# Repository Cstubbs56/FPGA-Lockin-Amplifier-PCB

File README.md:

# FPGA-Lockin-Amplifier-PCB
## Purpose
This PCB acts as both DAQ and a lock in amplifier for the Waterloo Rocketry 2026 fiber optic gyroscope payload. To accomplish this, it 
- Biases the fibre optic loop by outputting a sinusoid to a piezoelectric crystal via a DAC with fibre optic wrapped around the PZT.
- Reads the output of the interferometer through a photodiode into a transimpedance amplifier and ADC.
- Calculates I and Q components then exports to an SD card going through the microcontroller.

## Power Electronics
The PCB needs 24V, 5V, 3.3V, 2.5V, and 1.2V. The 24V is used for biasing the piezoelectric crystal, and goes through a 0-20V output 16 bit DAC. 5V and 3.3V are used for the analog and digital circuitry, while the 2.5V and 1.2V are solely for powering the FPGA.

## Analog Electronics
As mentioned, there is an ADC reading a transimpedance amplifier. The transimpedance amplifier was sized based on an estimated maxium output power from the interferometer of 20mW into a photodiode with an approximate response of 0.55A/W. The other side is the aforementioned DAC, which is setup to output 0-20V with a sinusoid from the FPGA.

## Logging
The FPGA being used does nt have enough extra space in the fabric to interact with a filesystem and therefore the FPGA sends results to the microcontroller to be held in RAM before outputting to the SD card. There is a piece of flash memory connected to the FPGA, but this is used for configuration.

## FPGA
Since the FPGA's non-volatile configuration memory can only be written to once, the FPGA is used with volatile configuration. This means it must configure itself each time it powers on. It uses SPI for configuration, which is hooked up to both a flash ROM and a SPI header that can be used for programming the memory from a computer.  

## Laser
The laser on the PCB is a 200mW optical power infrared laser. It draws typically around 300mA in operation.

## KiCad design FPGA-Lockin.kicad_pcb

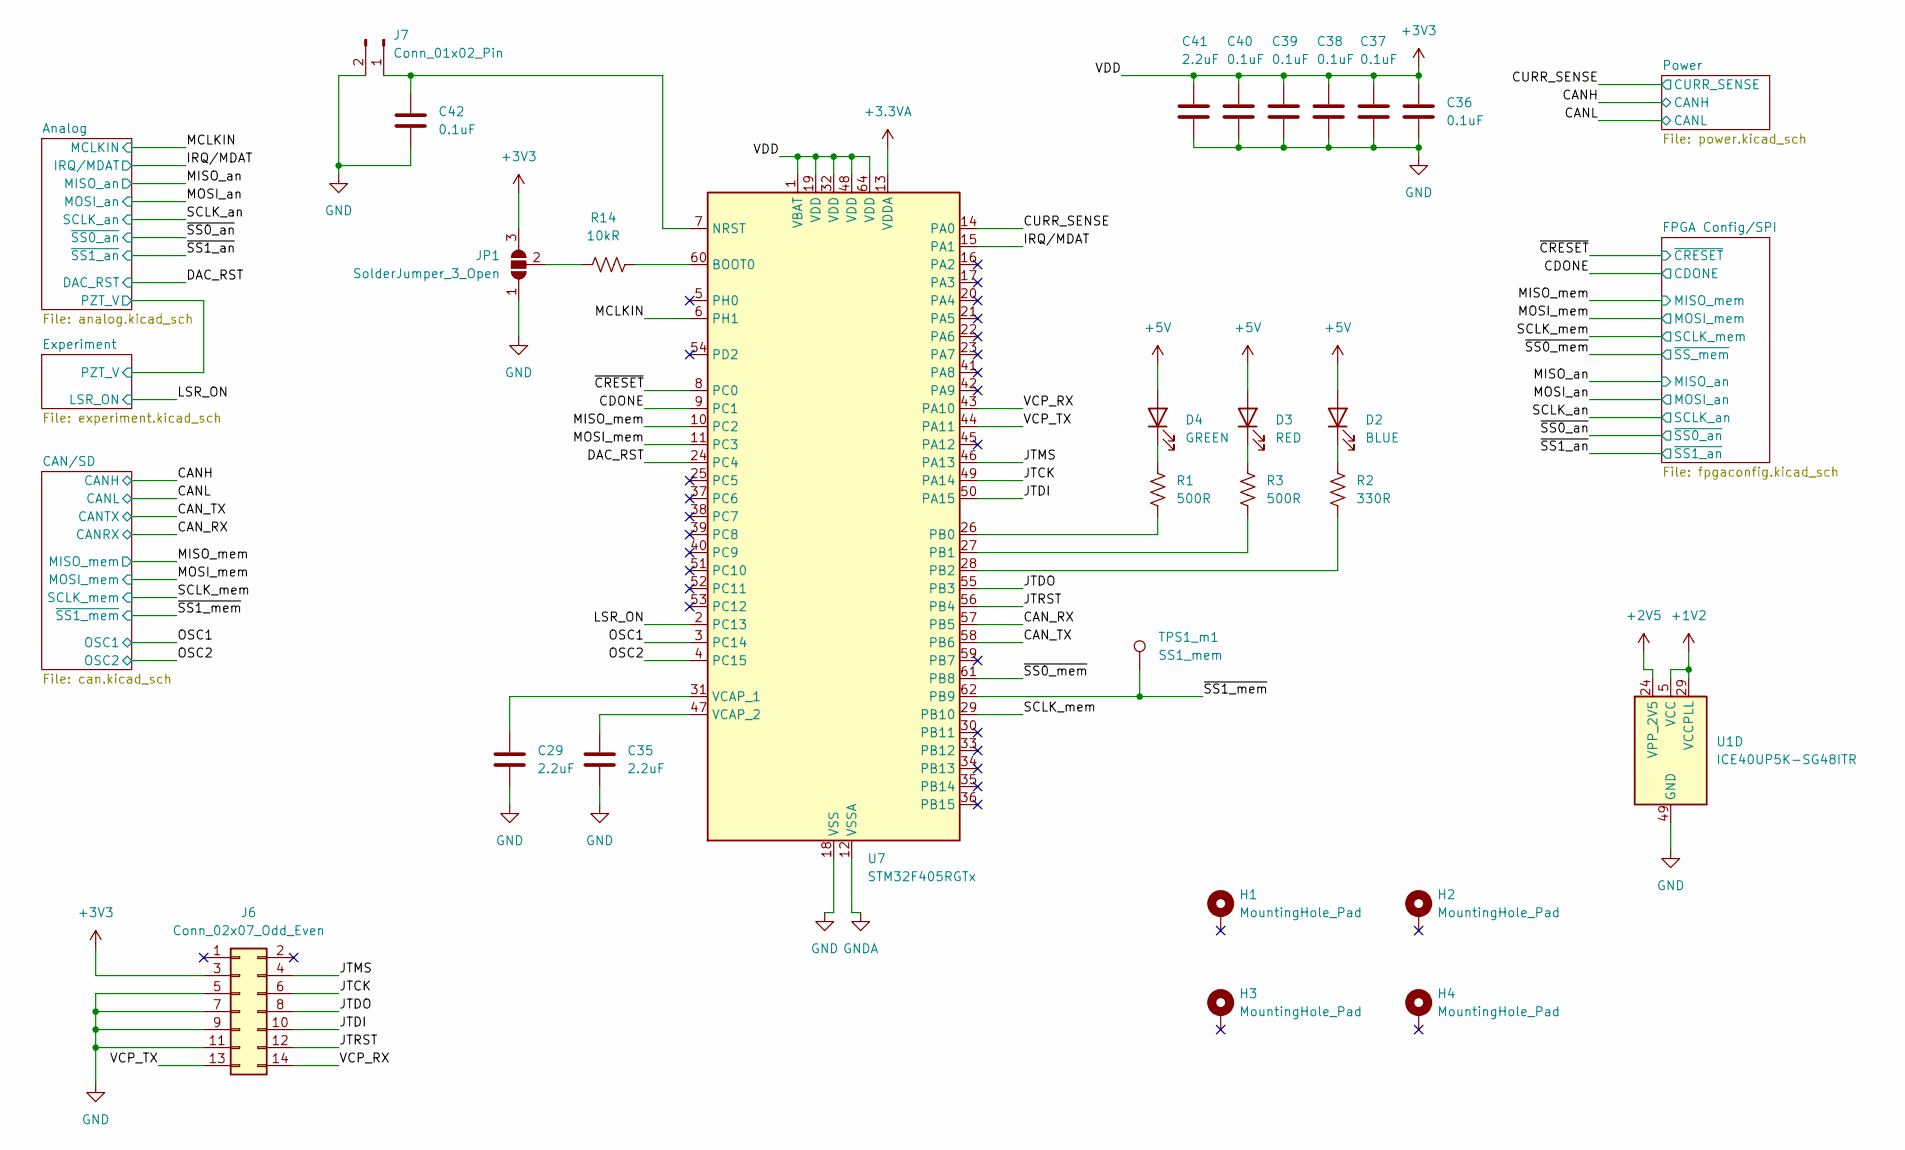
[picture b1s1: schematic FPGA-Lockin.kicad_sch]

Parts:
C29, C35, C41: 2.2uF; C_0805_2012Metric_Pad1.18x1.45mm_HandSolder
C36, C37, C38, C39, C40, C42: 0.1uF; C_0805_2012Metric_Pad1.18x1.45mm_HandSolder
D2: BLUE; LED_1206_3216Metric_Pad1.42x1.75mm_HandSolder
D3: RED; LED_1206_3216Metric_Pad1.42x1.75mm_HandSolder
D4: GREEN; LED_1206_3216Metric_Pad1.42x1.75mm_HandSolder
H1, H2, H3, H4: MountingHole_Pad; MountingHole_3.2mm_M3_Pad
J6: Conn_02x07_Odd_Even; PinSocket_2x07_P1.27mm_Vertical_SMD
J7: Conn_01x02_Pin; PinSocket_1x02_P2.54mm_Vertical
JP1: SolderJumper_3_Open; SolderJumper-3_P1.3mm_Open_RoundedPad1.0x1.5mm
R1, R3: 500R; R_0805_2012Metric_Pad1.20x1.40mm_HandSolder
R2: 330R; R_0805_2012Metric_Pad1.20x1.40mm_HandSolder
R14: 10kR; R_0805_2012Metric_Pad1.20x1.40mm_HandSolder
TPS1_m1: SS1_mem; TestPoint_Pad_D1.0mm
U1: ICE40UP5K-SG48ITR; QFN-48-1EP_7x7mm_P0.5mm_EP5.6x5.6mm
U7: STM32F405RGTx; LQFP-64_10x10mm_P0.5mm

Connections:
+1V2: U1.5 (VCC), U1.29 (VCCPLL), U1.30 (VCC); also elsewhere on the board
+2V5: U1.24 (VPP_2V5); also elsewhere on the board
+3.3VA: U7.13 (VDDA); also elsewhere on the board
+3V3: C36.1, C37.1, C38.1, C39.1, C40.1, C41.1, J6.3, JP1.3 (B), U7.1 (VBAT), U7.19 (VDD), U7.32 (VDD), U7.48 (VDD), U7.64 (VDD); also elsewhere on the board
+5V: D2.2 (A), D3.2 (A), D4.2 (A); also elsewhere on the board
/CAN_RX: U7.57 (PB5); also elsewhere on the board
/CAN_TX: U7.58 (PB6); also elsewhere on the board
/CDONE: U7.9 (PC1); also elsewhere on the board
/CURR_SENSE: U7.14 (PA0); also elsewhere on the board
/DAC_RST: U7.24 (PC4); also elsewhere on the board
/IRQ/MDAT: U7.15 (PA1); also elsewhere on the board
/JTCK: J6.6, U7.49 (PA14)
/JTDI: J6.10, U7.50 (PA15)
/JTDO: J6.8, U7.55 (PB3)
/JTMS: J6.4, U7.46 (PA13)
/JTRST: J6.12, U7.56 (PB4)
/LSR_ON: U7.2 (PC13); also elsewhere on the board
/MCLKIN: U7.6 (PH1); also elsewhere on the board
/MISO_mem: U7.10 (PC2); also elsewhere on the board
/MOSI_mem: U7.11 (PC3); also elsewhere on the board
/OSC1: U7.3 (PC14); also elsewhere on the board
/OSC2: U7.4 (PC15); also elsewhere on the board
/SCLK_mem: U7.29 (PB10); also elsewhere on the board
/VCP_RX: J6.14, U7.43 (PA10)
/VCP_TX: J6.13, U7.44 (PA11)
/~CRESET: U7.8 (PC0); also elsewhere on the board
/~SS0_mem: U7.61 (PB8); also elsewhere on the board
/~SS1_mem: TPS1_m1.1, U7.62 (PB9); also elsewhere on the board
GND: C29.2, C35.2, C36.2, C37.2, C38.2, C39.2, C40.2, C41.2, C42.2, J6.5, J6.7, J6.9, J6.11, J7.2, JP1.1 (A), U1.49 (GND), U7.18 (VSS), U7.63 (VSS); also elsewhere on the board
GNDA: U7.12 (VSSA); also elsewhere on the board
unnamed: D2.1 (K), R2.1
unnamed: D3.1 (K), R3.1
unnamed: D4.1 (K), R1.1
unnamed: C42.1, J7.1, U7.7 (NRST)
unnamed: JP1.2 (C), R14.2
unnamed: R14.1, U7.60 (BOOT0)
unnamed: R1.2, U7.26 (PB0)
unnamed: R3.2, U7.27 (PB1)
unnamed: R2.2, U7.28 (PB2)
unnamed: C29.1, U7.31 (VCAP_1)
unnamed: C35.1, U7.47 (VCAP_2)

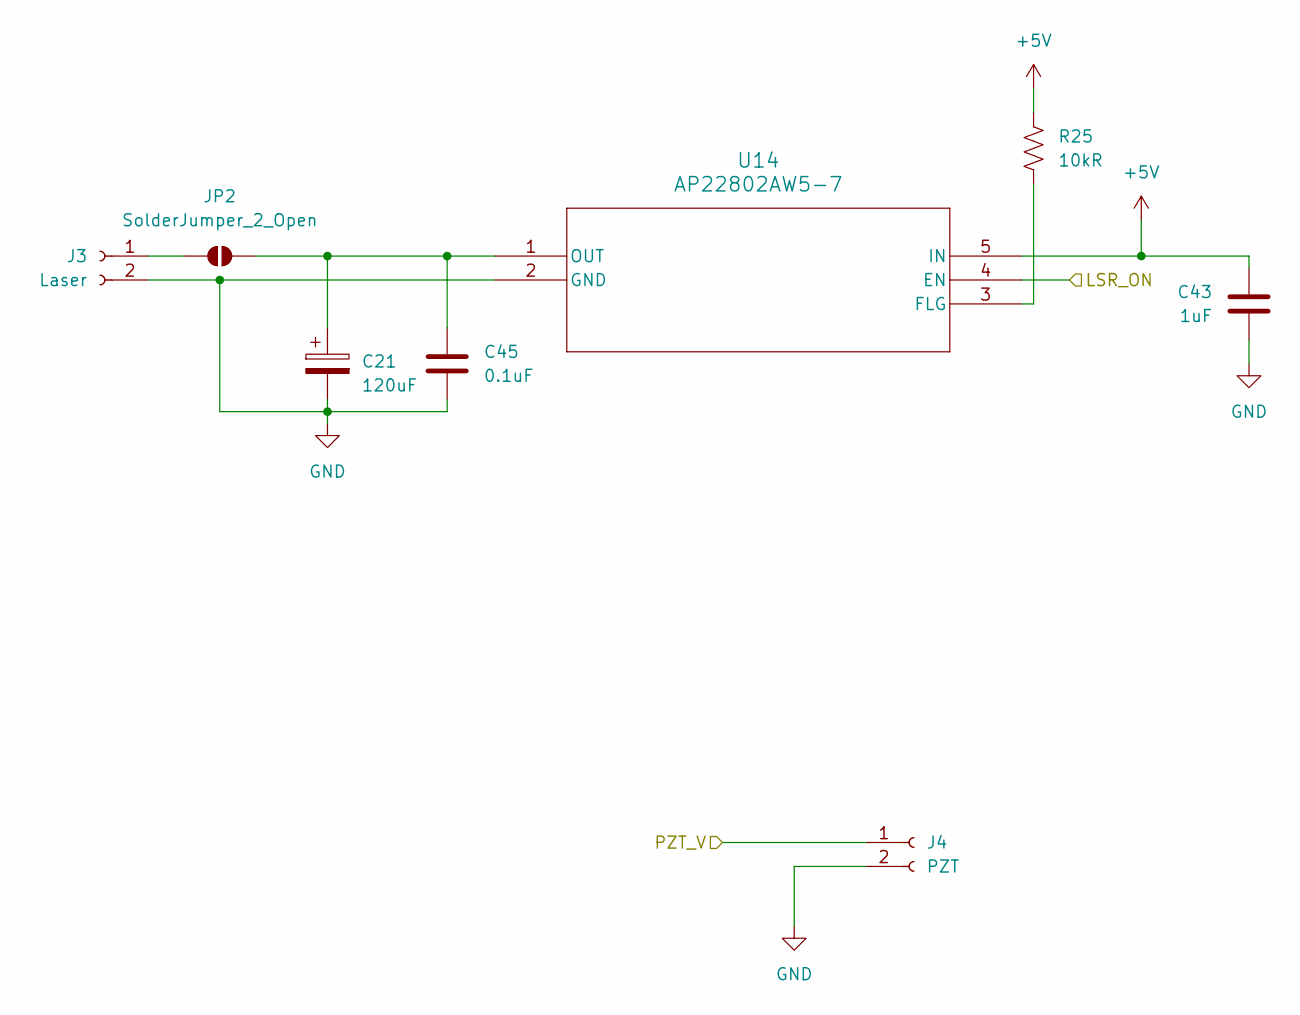
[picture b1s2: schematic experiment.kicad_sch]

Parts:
C21: 120uF; CP_EIA-7132-20_AVX-U_HandSolder
C43: 1uF; C_0805_2012Metric_Pad1.18x1.45mm_HandSolder
C45: 0.1uF; C_0805_2012Metric_Pad1.18x1.45mm_HandSolder
J3: Laser; 691137710002
J4: PZT; 691137710002
JP2: SolderJumper_2_Open; SolderJumper-2_P1.3mm_Open_RoundedPad1.0x1.5mm
R25: 10kR; R_0805_2012Metric_Pad1.20x1.40mm_HandSolder
U14: AP22802AW5-7; SOT25_DIO

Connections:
+5V: C43.2, R25.1, U14.5 (IN); also elsewhere on the board
/Analog/PZT_V: J4.1; also elsewhere on the board
/LSR_ON: U14.4 (EN); also elsewhere on the board
GND: C21.2, C43.1, C45.2, J3.2, J4.2, U14.2 (GND); also elsewhere on the board
unnamed: J3.1, JP2.2 (B)
unnamed: C21.1, C45.1, JP2.1 (A), U14.1 (OUT)
unnamed: R25.2, U14.3 (FLG)

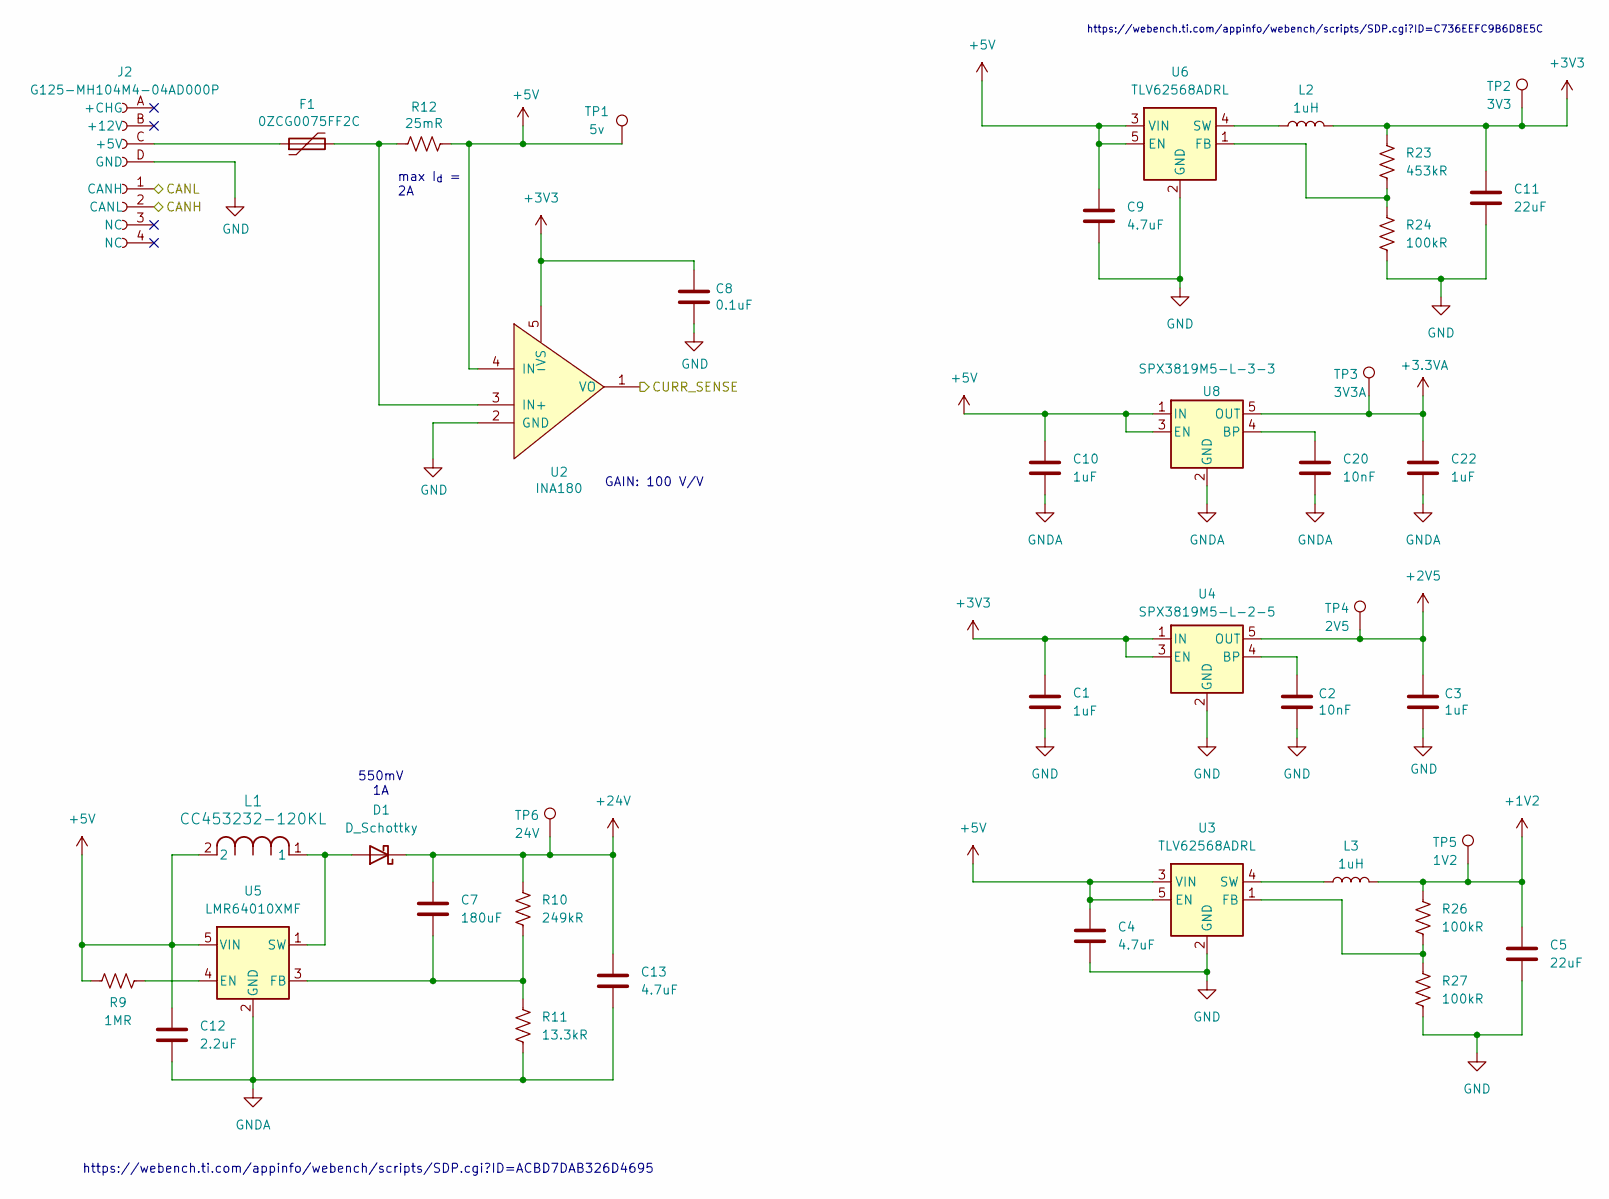
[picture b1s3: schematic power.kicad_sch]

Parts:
C1, C10, C22: 1uF; C_0805_2012Metric_Pad1.18x1.45mm_HandSolder
C2: 10nF; C_0805_2012Metric_Pad1.18x1.45mm_HandSolder; DigiKey 732-12169-1-ND
C3: 1uF; C_0805_2012Metric_Pad1.18x1.45mm_HandSolder; DigiKey 1276-6470-1-ND
C4, C9: 4.7uF; C_0805_2012Metric_Pad1.18x1.45mm_HandSolder
C5, C11: 22uF; C_0805_2012Metric_Pad1.18x1.45mm_HandSolder
C7: 180uF; C_1210_3225Metric_Pad1.33x2.70mm_HandSolder
C8: 0.1uF; C_0805_2012Metric_Pad1.18x1.45mm_HandSolder; DigiKey 311-1858-1-ND
C12: 2.2uF; C_0805_2012Metric_Pad1.18x1.45mm_HandSolder
C13: 4.7uF; C_1210_3225Metric_Pad1.33x2.70mm_HandSolder
C20: 10nF; C_0805_2012Metric_Pad1.18x1.45mm_HandSolder
D1: D_Schottky; DIO_RB051MM_ROM
F1: 0ZCG0075FF2C; Fuse_1812_4532Metric_Pad1.30x3.40mm_HandSolder; DigiKey F3732CT-ND
J2: G125-MH104M4-04AD000P; connector_Harwin_G125-MH104M4-04AD000P
L1: CC453232-120KL; IND_BOURNS_CC453232
L2, L3: 1uH; L_1206_3216Metric_Pad1.22x1.90mm_HandSolder
R9: 1MR; R_0805_2012Metric_Pad1.20x1.40mm_HandSolder
R10: 249kR; R_0805_2012Metric_Pad1.20x1.40mm_HandSolder
R11: 13.3kR; R_0805_2012Metric_Pad1.20x1.40mm_HandSolder
R12: 25mR; R_0805_2012Metric_Pad1.20x1.40mm_HandSolder; DigiKey WSLB-.20CT-ND
R23: 453kR; R_0805_2012Metric_Pad1.20x1.40mm_HandSolder
R24, R26, R27: 100kR; R_0805_2012Metric_Pad1.20x1.40mm_HandSolder
TP1: 5v; TestPoint_Pad_1.5x1.5mm
TP2: 3V3; TestPoint_Pad_1.5x1.5mm
TP3: 3V3A; TestPoint_Pad_1.5x1.5mm
TP4: 2V5; TestPoint_Pad_1.5x1.5mm
TP5: 1V2; TestPoint_Pad_1.5x1.5mm
TP6: 24V; TestPoint_Pad_1.5x1.5mm
U2: INA180; SOT-23-5_HandSoldering; DigiKey 296-INA180A3QDBVRQ1CT-ND
U3, U6: TLV62568ADRL; SOT-563
U4: SPX3819M5-L-2-5; SOT-23-5
U5: LMR64010XMF; SOT-23-5
U8: SPX3819M5-L-3-3; SOT-23-5_HandSoldering; DigiKey 1016-1873-1-ND

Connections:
+1V2: C5.1, L3.2, R26.1, TP5.1; also elsewhere on the board
+2V5: C3.1, TP4.1, U4.5 (OUT); also elsewhere on the board
+3.3VA: C22.1, TP3.1, U8.5 (OUT); also elsewhere on the board
+3V3: C1.1, C8.1, C11.1, L2.2, R23.1, TP2.1, U2.5 (VS), U4.1 (IN), U4.3 (EN); also elsewhere on the board
+5V: C4.1, C9.1, C10.1, C12.1, L1.2, R9.2, R12.1, TP1.1, U2.4 (IN-), U3.3 (VIN), U3.5 (EN), U5.5 (VIN), U6.3 (VIN), U6.5 (EN), U8.1 (IN), U8.3 (EN); also elsewhere on the board
+24V: C7.1, C13.1, D1.1 (K), R10.1, TP6.1; also elsewhere on the board
/CANH: J2.2 (CANL); also elsewhere on the board
/CANL: J2.1 (CANH); also elsewhere on the board
/CURR_SENSE: U2.1 (VO); also elsewhere on the board
GND: C1.2, C2.2, C3.2, C4.2, C5.2, C8.2, C9.2, C11.2, J2.D (GND), R24.2, R27.2, U2.2 (GND), U3.2 (GND), U4.2 (GND), U6.2 (GND); also elsewhere on the board
GNDA: C10.2, C12.2, C13.2, C20.2, C22.2, R11.2, U5.2 (GND), U8.2 (GND); also elsewhere on the board
unnamed: D1.2 (A), L1.1, U5.1 (SW)
unnamed: F1.1, J2.C (+5V)
unnamed: F1.2, R12.2, U2.3 (IN+)
unnamed: R26.2, R27.1, U3.1 (FB)
unnamed: L3.1, U3.4 (SW)
unnamed: C2.1, U4.4 (BP)
unnamed: R9.1, U5.4 (EN)
unnamed: C7.2, R10.2, R11.1, U5.3 (FB)
unnamed: R23.2, R24.1, U6.1 (FB)
unnamed: L2.1, U6.4 (SW)
unnamed: C20.1, U8.4 (BP)

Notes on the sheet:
GAIN: 100 V/V
https://webench.ti.com/appinfo/webench/scripts/SDP.cgi?ID=C736EEFC9B6D8E5C
max I_{d} = 2A
550mV 1A
https://webench.ti.com/appinfo/webench/scripts/SDP.cgi?ID=ACBD7DAB326D4695

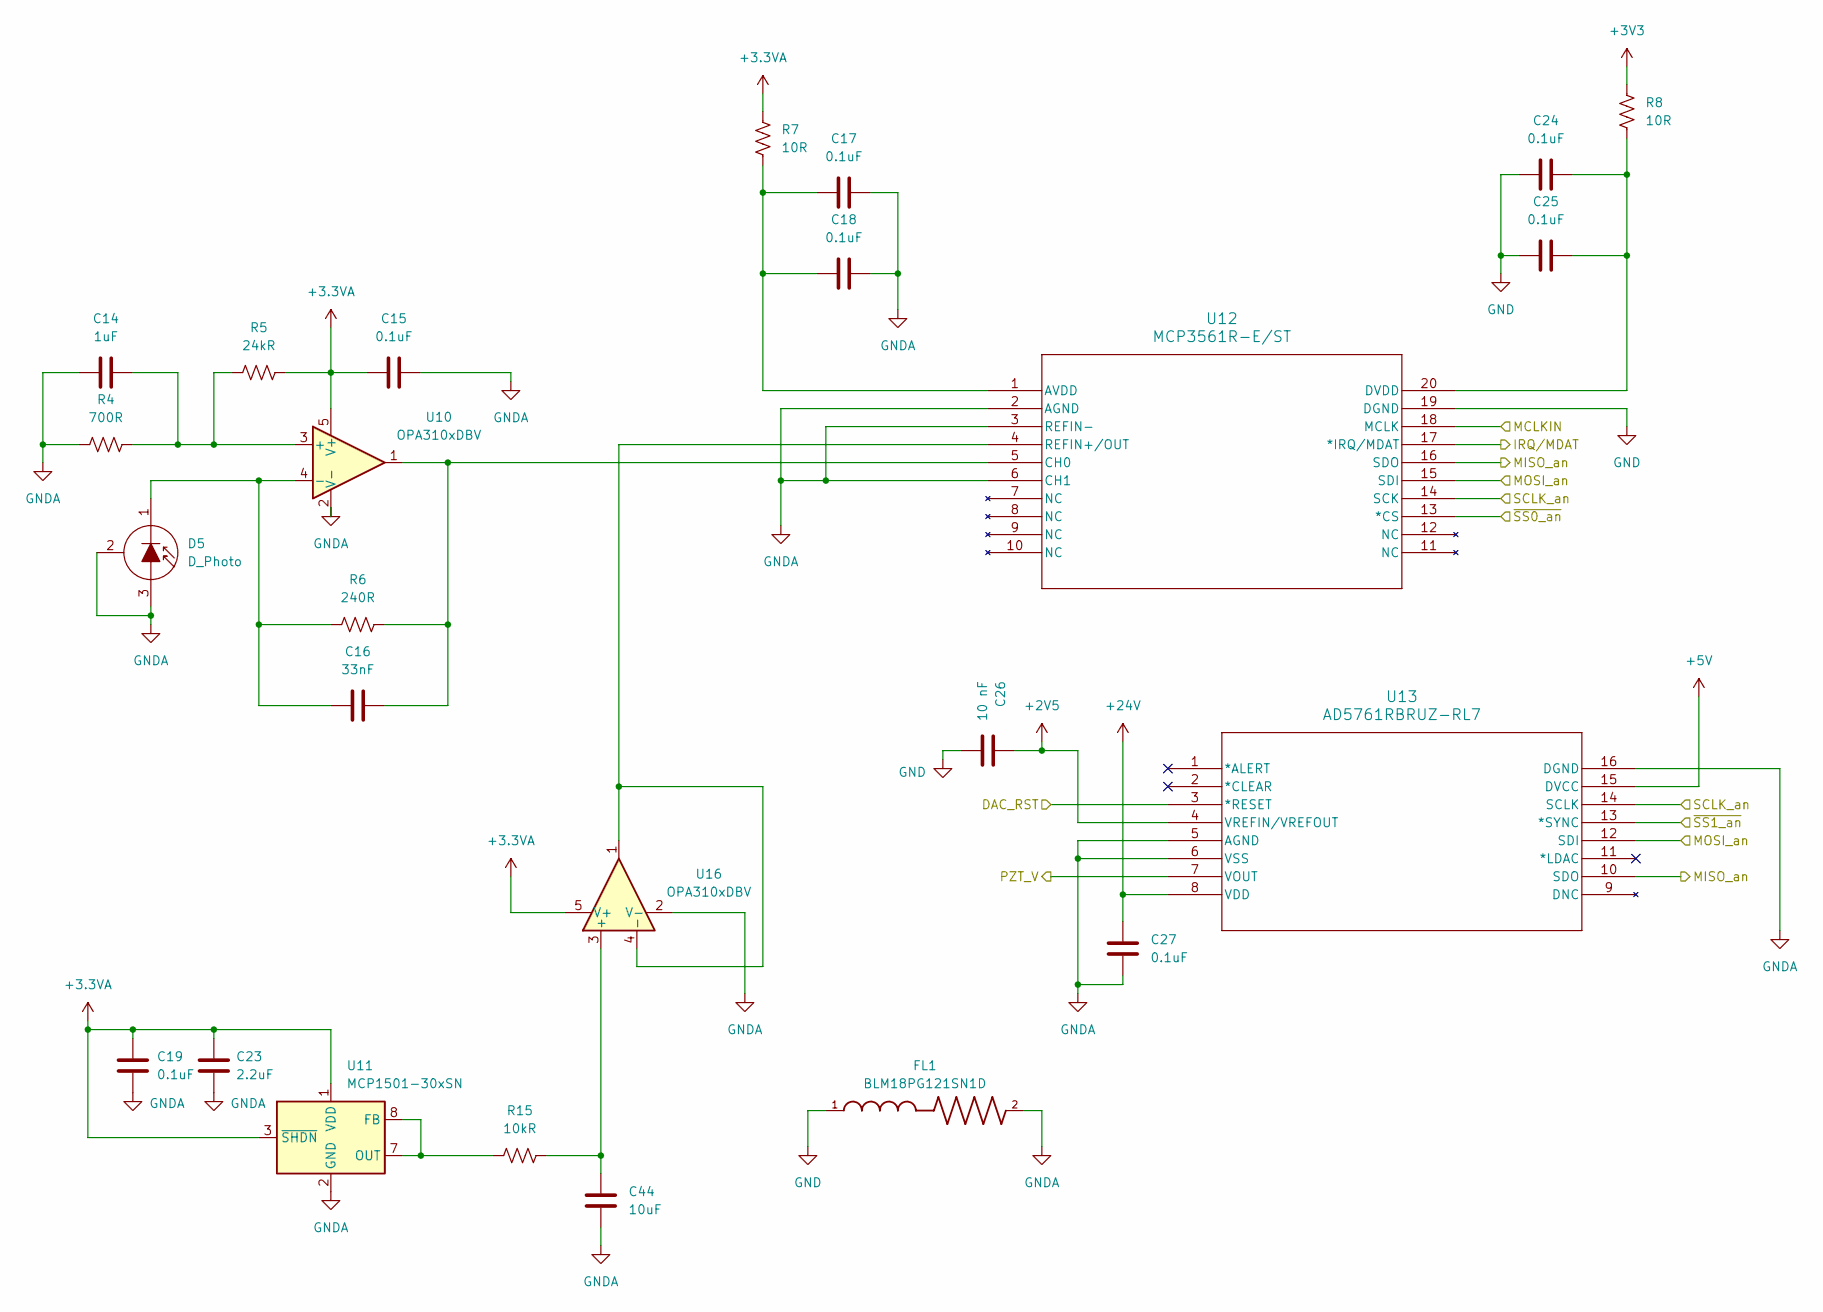
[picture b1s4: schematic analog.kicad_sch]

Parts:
C14: 1uF; C_0805_2012Metric_Pad1.18x1.45mm_HandSolder
C15, C17, C18, C19, C24, C25: 0.1uF; C_0805_2012Metric_Pad1.18x1.45mm_HandSolder
C16: 33nF; C_0805_2012Metric_Pad1.18x1.45mm_HandSolder
C23: 2.2uF; C_0805_2012Metric_Pad1.18x1.45mm_HandSolder
C26: 10 nF; C_0805_2012Metric_Pad1.18x1.45mm_HandSolder
C27: 0.1uF; C_1210_3225Metric_Pad1.33x2.70mm_HandSolder
C44: 10uF; C_0805_2012Metric_Pad1.18x1.45mm_HandSolder
D5: D_Photo; TO-5-3
FL1: BLM18PG121SN1D; BEADC1608X95N
R4: 700R; R_0805_2012Metric_Pad1.20x1.40mm_HandSolder
R5: 24kR; R_0805_2012Metric_Pad1.20x1.40mm_HandSolder
R6: 240R; R_0805_2012Metric_Pad1.20x1.40mm_HandSolder
R7, R8: 10R; R_0805_2012Metric_Pad1.20x1.40mm_HandSolder
R15: 10kR; R_0805_2012Metric_Pad1.20x1.40mm_HandSolder
U10, U16: OPA310xDBV; SOT-23-5
U11: MCP1501-30xSN; SOIC-8_3.9x4.9mm_P1.27mm
U12: MCP3561R-E/ST; TSSOP20_ST_MCH
U13: AD5761RBRUZ-RL7; RU-16_ADI

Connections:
+2V5: C26.1, U13.4 (VREFIN/VREFOUT); also elsewhere on the board
+3.3VA: C15.2, C19.1, C23.1, R5.2, R7.1, U10.5 (V+), U11.1 (VDD), U11.3 (~SHDN), U16.5 (V+); also elsewhere on the board
+3V3: R8.1; also elsewhere on the board
+5V: U13.15 (DVCC); also elsewhere on the board
+24V: C27.1, U13.8 (VDD); also elsewhere on the board
/Analog/PZT_V: U13.7 (VOUT); also elsewhere on the board
/DAC_RST: U13.3 (*RESET); also elsewhere on the board
/IRQ/MDAT: U12.17 (*IRQ/MDAT); also elsewhere on the board
/MCLKIN: U12.18 (MCLK); also elsewhere on the board
/MISO_an: U12.16 (SDO), U13.10 (SDO); also elsewhere on the board
/MOSI_an: U12.15 (SDI), U13.12 (SDI); also elsewhere on the board
/SCLK_an: U12.14 (SCK), U13.14 (SCLK); also elsewhere on the board
/~SS0_an: U12.13 (*CS); also elsewhere on the board
/~SS1_an: U13.13 (*SYNC); also elsewhere on the board
GND: C24.1, C25.1, C26.2, FL1.1, U12.19 (DGND); also elsewhere on the board
GNDA: C14.2, C15.1, C17.2, C18.2, C19.2, C23.2, C27.2, C44.2, D5.2 (C), D5.3 (A), FL1.2, R4.1, U10.2 (V-), U11.2 (GND), U11.4 (GND), U11.5 (GND), U11.6 (GND), U12.2 (AGND), U12.3 (REFIN-), U12.6 (CH1), U13.5 (AGND), U13.6 (VSS), U13.16 (DGND), U16.2 (V-); also elsewhere on the board
unnamed: C16.2, D5.1 (K), R6.1, U10.4 (-)
unnamed: C14.1, R4.2, R5.1, U10.3 (+)
unnamed: R15.1, U11.7 (OUT), U11.8 (FB)
unnamed: C17.1, C18.1, R7.2, U12.1 (AVDD)
unnamed: C16.1, R6.2, U10.1, U12.5 (CH0)
unnamed: C24.2, C25.2, R8.2, U12.20 (DVDD)
unnamed: U12.4 (REFIN+/OUT), U16.1, U16.4 (-)
unnamed: C44.1, R15.2, U16.3 (+)

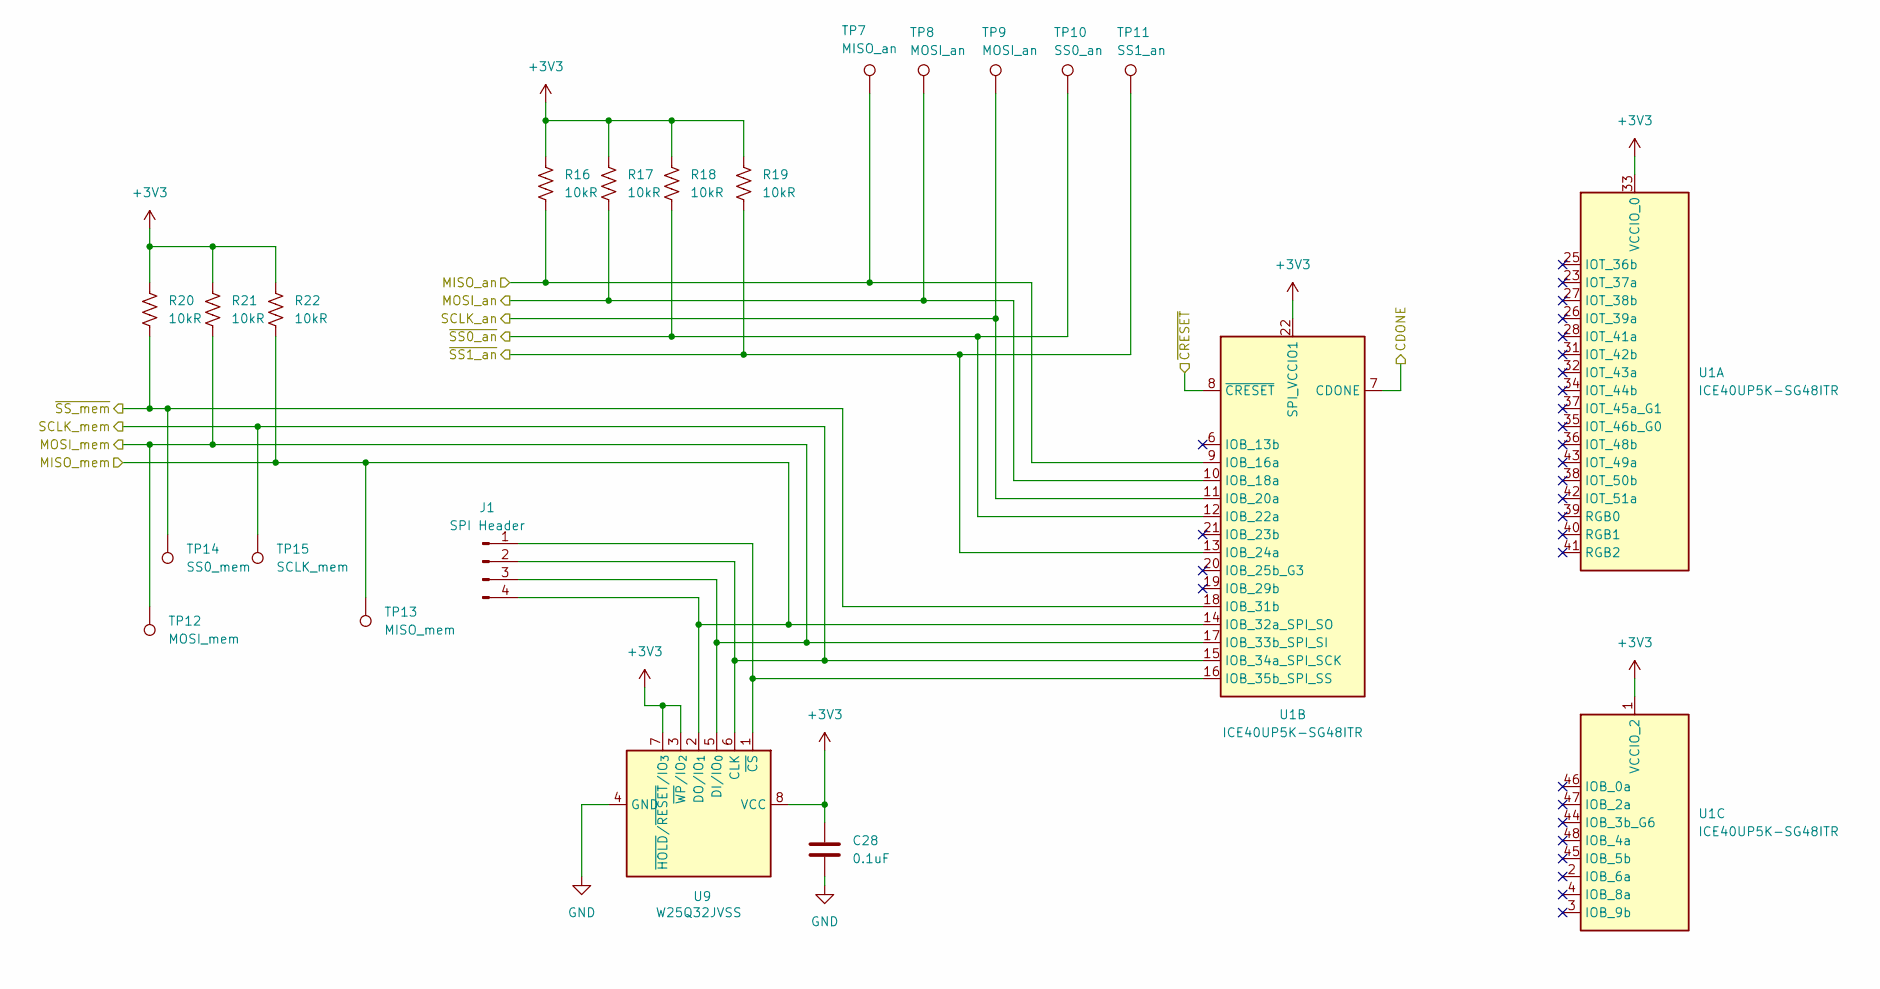
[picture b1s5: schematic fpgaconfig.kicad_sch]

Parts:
C28: 0.1uF; C_0805_2012Metric_Pad1.18x1.45mm_HandSolder
J1: SPI Header; PinHeader_1x04_P2.54mm_Vertical
R16, R17, R18, R19, R20, R21, R22: 10kR; R_0805_2012Metric_Pad1.20x1.40mm_HandSolder
TP7: MISO_an; TestPoint_Pad_D1.0mm
TP8, TP9: MOSI_an; TestPoint_Pad_D1.0mm
TP10: SS0_an; TestPoint_Pad_D1.0mm
TP11: SS1_an; TestPoint_Pad_D1.0mm
TP12: MOSI_mem; TestPoint_Pad_D1.0mm
TP13: MISO_mem; TestPoint_Pad_D1.0mm
TP14: SS0_mem; TestPoint_Pad_D1.0mm
TP15: SCLK_mem; TestPoint_Pad_D1.0mm
U1: ICE40UP5K-SG48ITR; QFN-48-1EP_7x7mm_P0.5mm_EP5.6x5.6mm
U9: W25Q32JVSS; SOIC-8_5.3x5.3mm_P1.27mm

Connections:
+3V3: C28.1, R16.1, R17.1, R18.1, R19.1, R20.1, R21.1, R22.1, U1.1 (VCCIO_2), U1.22 (SPI_VCCIO1), U1.33 (VCCIO_0), U9.3 (~WP/IO_{2}), U9.7 (~HOLD/~RESET/IO_{3}), U9.8 (VCC); also elsewhere on the board
/CDONE: U1.7 (CDONE); also elsewhere on the board
/MISO_an: R16.2, TP7.1, U1.9 (IOB_16a); also elsewhere on the board
/MISO_mem: J1.4, R22.2, TP13.1, U1.14 (IOB_32a_SPI_SO), U9.2 (DO/IO_{1}); also elsewhere on the board
/MOSI_an: R17.2, TP8.1, U1.10 (IOB_18a); also elsewhere on the board
/MOSI_mem: J1.3, R21.2, TP12.1, U1.17 (IOB_33b_SPI_SI), U9.5 (DI/IO_{0}); also elsewhere on the board
/SCLK_an: TP9.1, U1.11 (IOB_20a); also elsewhere on the board
/SCLK_mem: J1.2, TP15.1, U1.15 (IOB_34a_SPI_SCK), U9.6 (CLK); also elsewhere on the board
/~CRESET: U1.8 (~CRESET); also elsewhere on the board
/~SS0_an: R18.2, TP10.1, U1.12 (IOB_22a); also elsewhere on the board
/~SS0_mem: R20.2, TP14.1, U1.18 (IOB_31b); also elsewhere on the board
/~SS1_an: R19.2, TP11.1, U1.13 (IOB_24a); also elsewhere on the board
GND: C28.2, U9.4 (GND); also elsewhere on the board
unnamed: J1.1, U1.16 (IOB_35b_SPI_SS), U9.1 (~CS)

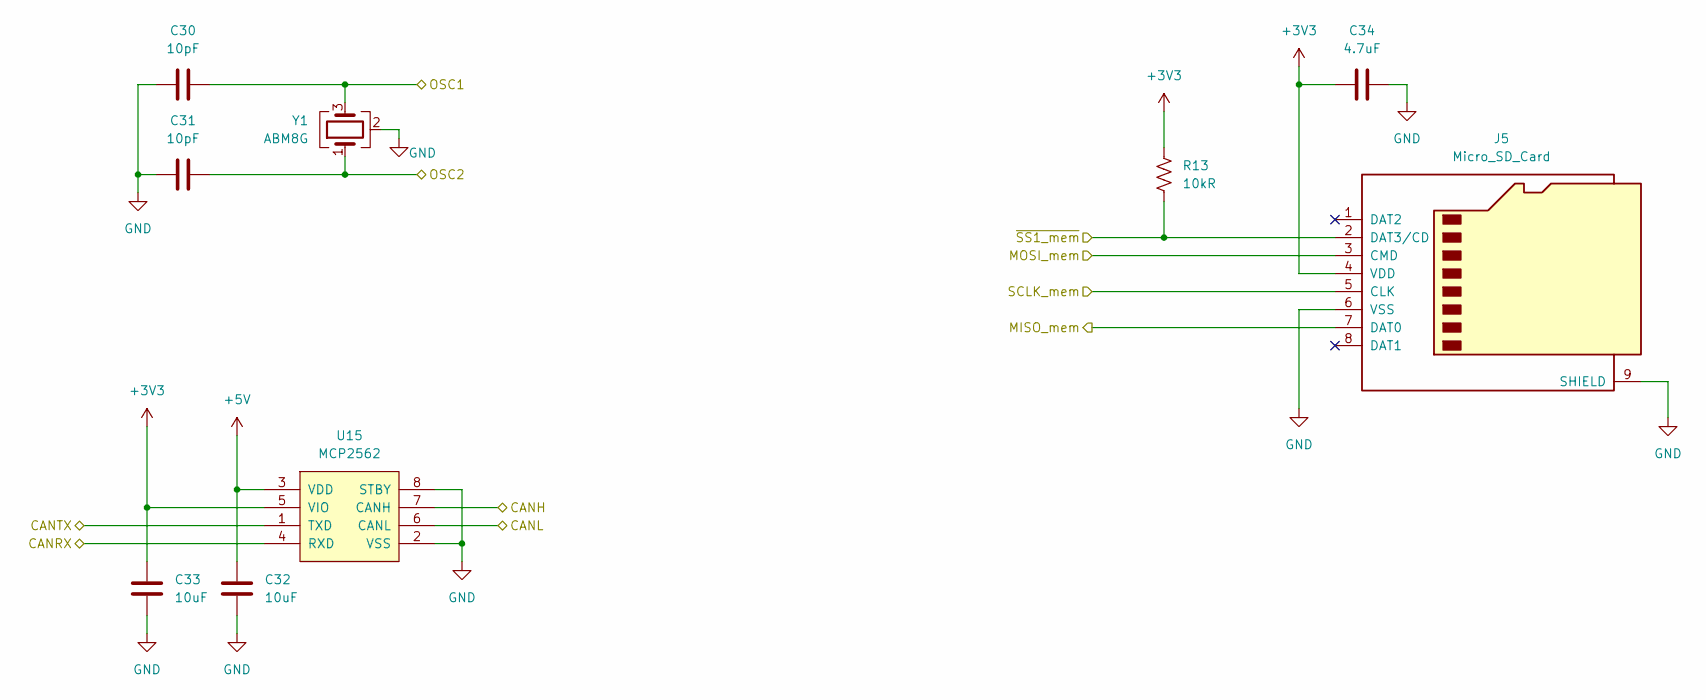
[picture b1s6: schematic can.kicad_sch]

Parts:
C30, C31: 10pF; C_0805_2012Metric_Pad1.18x1.45mm_HandSolder
C32, C33: 10uF; C_0805_2012Metric_Pad1.18x1.45mm_HandSolder
C34: 4.7uF; C_0805_2012Metric_Pad1.18x1.45mm_HandSolder
J5: Micro_SD_Card; microSD_Molex_WM6698CT-ND
R13: 10kR; R_0805_2012Metric_Pad1.20x1.40mm_HandSolder
U15: MCP2562; SOIC-8_3.9x4.9mm_P1.27mm
Y1: ABM8G; Crystal_SMD_Abracon_ABM8G-4Pin_3.2x2.5mm

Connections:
+3V3: C33.1, C34.2, J5.4 (VDD), R13.1, U15.5 (VIO); also elsewhere on the board
+5V: C32.1, U15.3 (VDD); also elsewhere on the board
/CANH: U15.7 (CANH); also elsewhere on the board
/CANL: U15.6 (CANL); also elsewhere on the board
/CAN_RX: U15.4 (RXD); also elsewhere on the board
/CAN_TX: U15.1 (TXD); also elsewhere on the board
/MISO_mem: J5.7 (DAT0); also elsewhere on the board
/MOSI_mem: J5.3 (CMD); also elsewhere on the board
/OSC1: C30.2, Y1.3; also elsewhere on the board
/OSC2: C31.2, Y1.1; also elsewhere on the board
/SCLK_mem: J5.5 (CLK); also elsewhere on the board
/~SS1_mem: J5.2 (DAT3/CD), R13.2; also elsewhere on the board
GND: C30.1, C31.1, C32.2, C33.2, C34.1, J5.6 (VSS), J5.9 (SHIELD), U15.2 (VSS), U15.8 (STBY), Y1.2 (G), Y1.4 (G); also elsewhere on the board

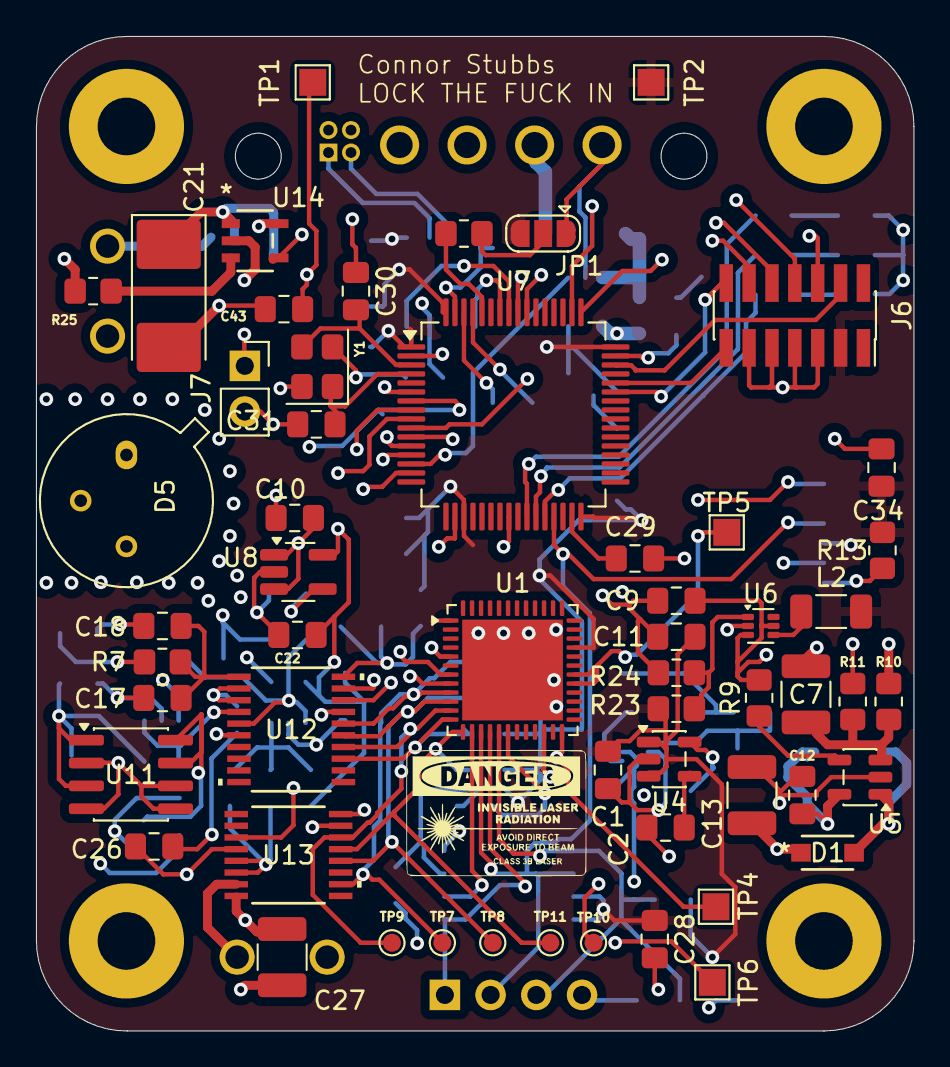
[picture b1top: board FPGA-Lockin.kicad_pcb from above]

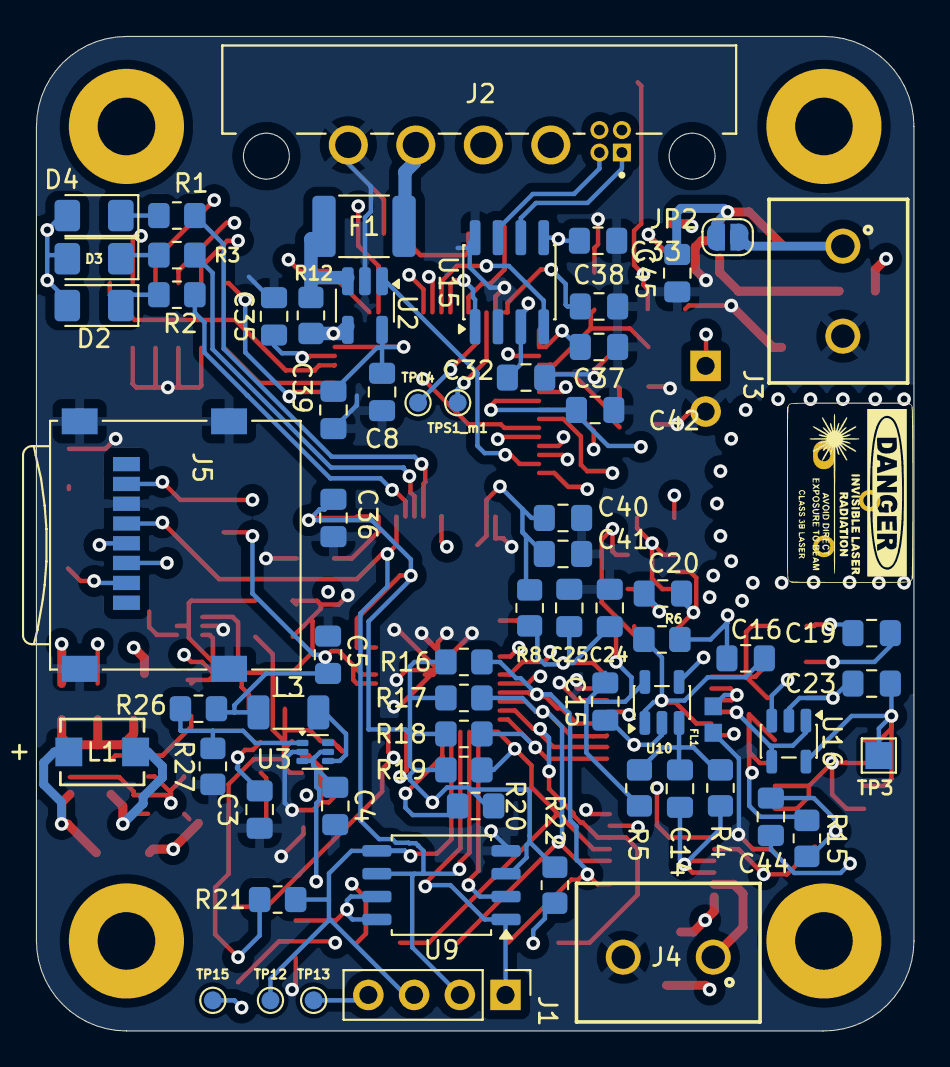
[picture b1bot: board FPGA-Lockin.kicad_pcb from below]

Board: 4 copper layers, 48.8 x 55.2 mm, 127 parts (67 on the bottom side), 73 nets.

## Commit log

2026-03-04 Fix Pranav review suggestions
2026-03-10 Fix review suggestions from non-fpga board
2026-03-10 Add gitignore
2026-03-10 Fix random files
2026-03-12 Fix layout errors after reviewing
2026-03-12 Fix diode
2026-03-16 Gerbers
2026-03-16 Fix everything based on component availabilty
